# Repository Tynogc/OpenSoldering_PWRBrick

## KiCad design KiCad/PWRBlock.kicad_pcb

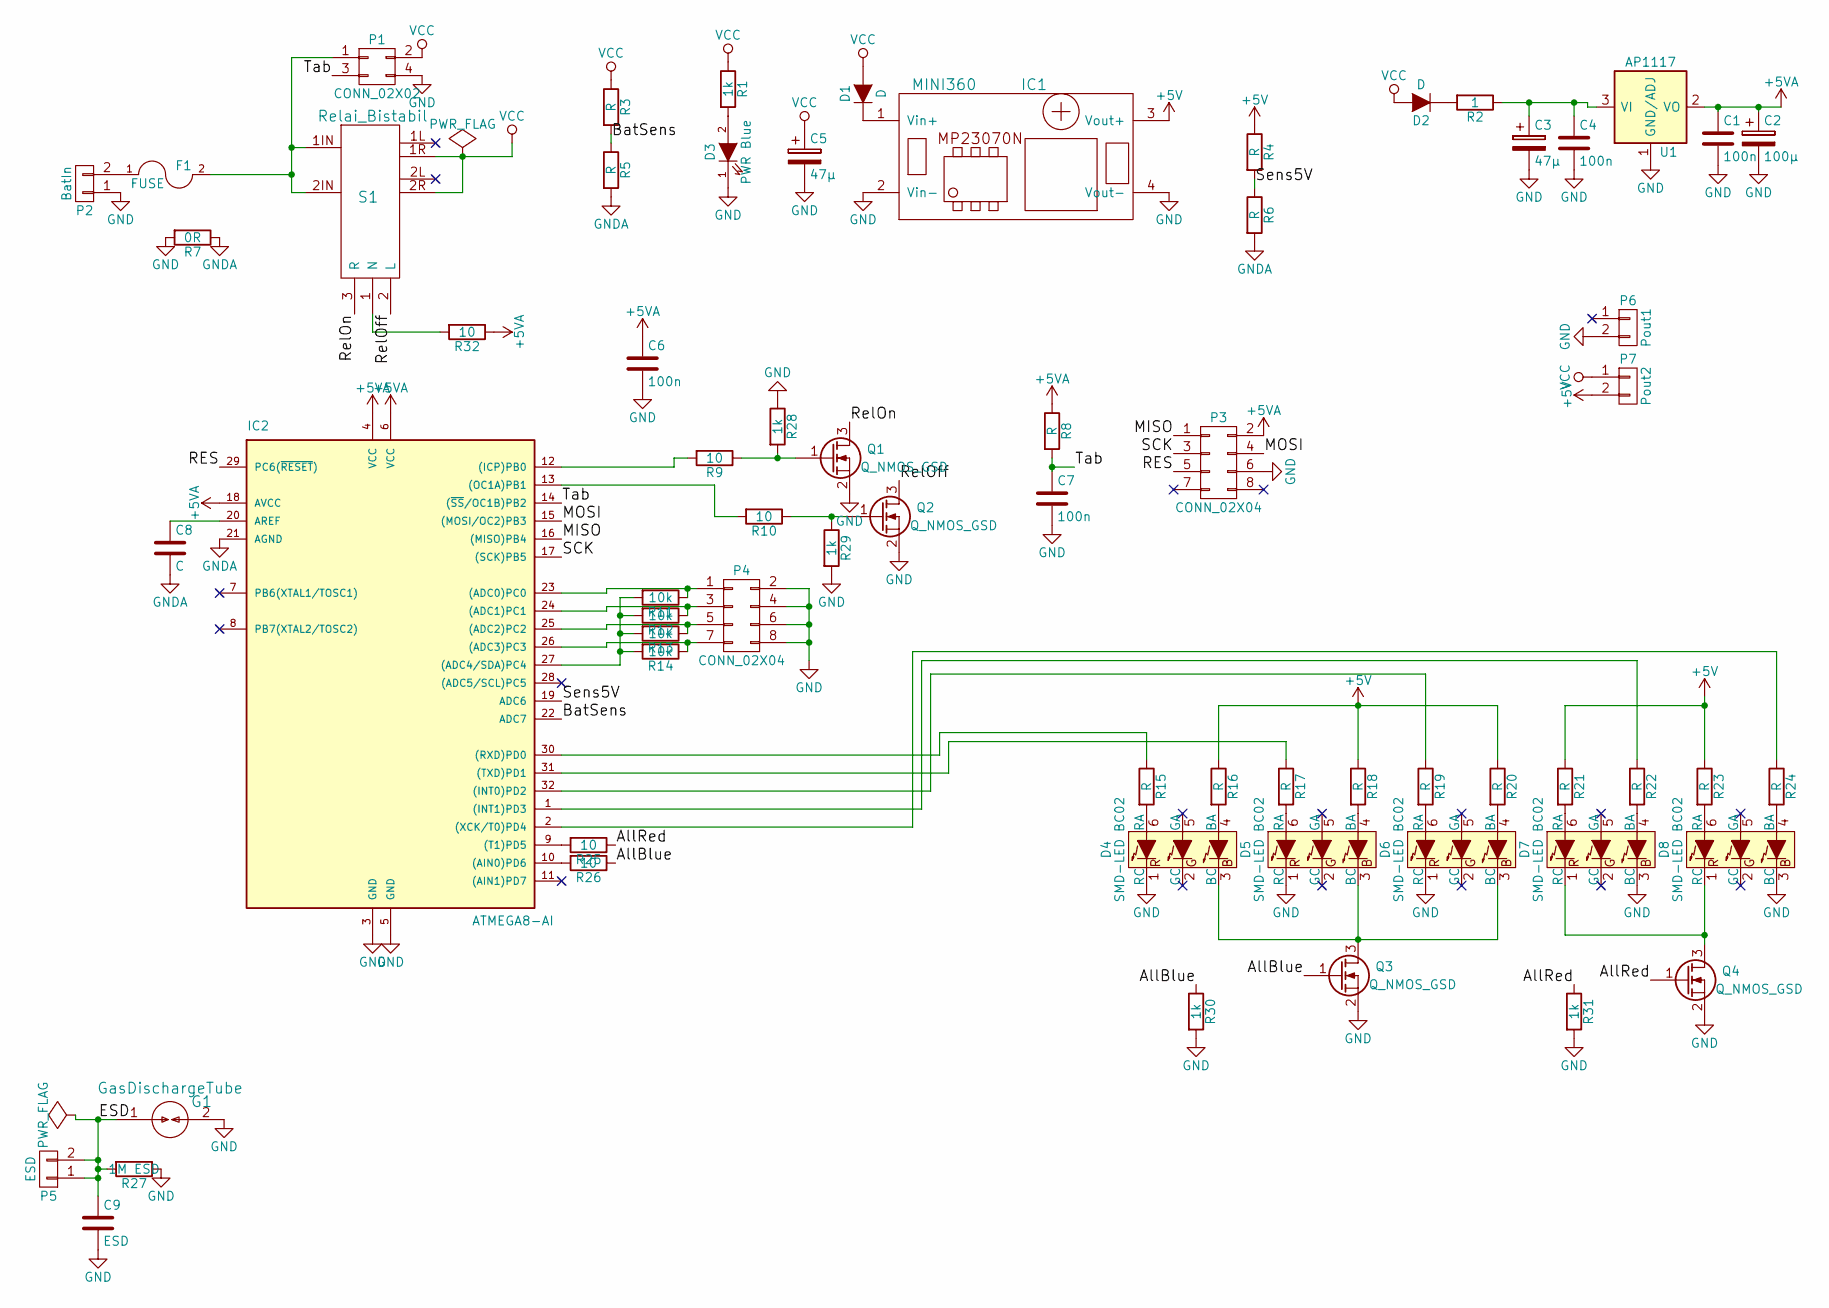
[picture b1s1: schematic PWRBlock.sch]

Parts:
C1, C4, C6, C7: 100n; C_0805
C2: 100µ; C_0805
C3, C5: 47µ; C_Radial_D10_L20_P2.5-5
C8: C; C_0805
C9: ESD; C_Disc_D6_P5
D1, D2: D; SMA-SMB_Universal_Handsoldering
D3: PWR Blue; LED-5MM
D4, D5, D6, D7, D8: SMD-LED BC02; LRTB_G6TG
F1: FUSE; Fuseholder5x20
G1: GasDischargeTube; Socket_Strip_Straight_1x02
IC1: MINI360; Mini360
IC2: ATMEGA8-AI; TQFP-32_7x7mm_Pitch0.8mm
P1: CONN_02X02; Socket_Strip_Straight_2x02
P2: BatIn; Screw_Connector_5,08mm_x2
P3, P4: CONN_02X04; Pin_Header_Straight_2x04
P5: ESD; Screw_Connector_5,08mm_x2
P6: Pout1; Screw_Connector_5,08mm_x2
P7: Pout2; Screw_Connector_5,08mm_x2
Q1, Q2, Q3, Q4: Q_NMOS_GSD; SOT-23_Handsoldering
R1, R28, R29, R30, R31: 1k; R_0805
R2: 1; R_0805
R3, R4, R5, R6, R8, R15, R16, R17, R18, R19, R20, R21, R22, R23, R24: R; R_0805
R7: 0R; R_0805
R9, R10, R25, R26, R32: 10; R_0805
R11, R12, R13, R14: 10k; R_0805
R27: 1M ESD; Resistor_Horizontal_RM15mm
S1: Relai_Bistabil; Relay_DPDT_Schrack-RT2_RM5mm
U1: AP1117; SOT223_GND_VO_VI

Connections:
+5V: IC1.3 (Vout+), P7.2, R4.1, R16.1, R18.1, R20.1, R21.1, R23.1
+5VA: C1.1, C2.1, C6.1, IC2.4 (VCC), IC2.6 (VCC), IC2.18 (AVCC), P3.2, R8.1, R32.1, R32.2, S1.1 (N), U1.2 (VO)
/AllBlue: Q3.1 (G), R26.1, R30.1
/AllRed: Q4.1 (G), R25.1, R31.1
/BatSens: IC2.22 (ADC7), R3.2, R5.1
/ESD: C9.1, G1.1, P5.1, P5.2, R27.2
/MISO: IC2.16 ((MISO)PB4), P3.1
/MOSI: IC2.15 ((MOSI/OC2)PB3), P3.4
/RES: IC2.29 (PC6(~RESET~)), P3.5
/RelOff: Q2.3 (D), S1.2 (L)
/RelOn: Q1.3 (D), S1.3 (R)
/SCK: IC2.17 ((SCK)PB5), P3.3
/Sens5V: IC2.19 (ADC6), R4.2, R6.1
/Tab: C7.1, IC2.14 ((~SS~/OC1B)PB2), P1.3, R8.2
GND: C1.2, C2.2, C3.2, C4.2, C5.2, C6.2, C7.2, C9.2, D3.1 (K), D4.1 (RC), D5.1 (RC), D6.1 (RC), D7.3 (BC), D8.3 (BC), G1.2, IC1.2 (Vin-), IC1.4 (Vout-), IC2.3 (GND), IC2.5 (GND), P1.4, P2.1, P3.6, P4.2, P4.4, P4.6, P4.8, P6.2, Q1.2 (S), Q2.2 (S), Q3.2 (S), Q4.2 (S), R7.2, R27.1, R28.1, R29.2, R30.2, R31.2, U1.1 (GND/ADJ)
GNDA: C8.2, IC2.21 (AGND), R5.2, R6.2, R7.1
unnamed: C3.1, C4.1, R2.1, U1.3 (VI)
unnamed: C8.1, IC2.20 (AREF)
unnamed: D1.1 (K), IC1.1 (Vin+)
unnamed: D2.1 (K), R2.2
unnamed: D3.2 (A), R1.2
unnamed: D4.3 (BC), D5.3 (BC), D6.3 (BC), Q3.3 (D)
unnamed: D4.4 (BA), R16.2
unnamed: D4.6 (RA), R15.2
unnamed: D5.4 (BA), R18.2
unnamed: D5.6 (RA), R17.2
unnamed: D6.4 (BA), R20.2
unnamed: D6.6 (RA), R19.2
unnamed: D7.1 (RC), D8.1 (RC), Q4.3 (D)
unnamed: D7.4 (BA), R22.2
unnamed: D7.6 (RA), R21.2
unnamed: D8.4 (BA), R24.2
unnamed: D8.6 (RA), R23.2
unnamed: F1.1, P2.2
unnamed: F1.2, P1.1, S1.1IN, S1.2IN
unnamed: IC2.1 ((INT1)PD3), R22.1
unnamed: IC2.2 ((XCK/T0)PD4), R24.1
unnamed: IC2.9 ((T1)PD5), R25.2
unnamed: IC2.10 ((AIN0)PD6), R26.2
unnamed: IC2.12 ((ICP)PB0), R9.2
unnamed: IC2.13 ((OC1A)PB1), R10.2
unnamed: IC2.23 ((ADC0)PC0), P4.1, R11.1
unnamed: IC2.24 ((ADC1)PC1), P4.3, R12.1
unnamed: IC2.25 ((ADC2)PC2), P4.5, R13.1
unnamed: IC2.26 ((ADC3)PC3), P4.7, R14.1
unnamed: IC2.27 ((ADC4/SDA)PC4), R11.2, R12.2, R13.2, R14.2
unnamed: IC2.30 ((RXD)PD0), R15.1
unnamed: IC2.31 ((TXD)PD1), R17.1
unnamed: IC2.32 ((INT0)PD2), R19.1
unnamed: Q1.1 (G), R9.1, R28.2
unnamed: Q2.1 (G), R10.1, R29.1
VCC: C5.1, D1.2 (A), D2.2 (A), P1.2, P7.1, R1.1, R3.1, S1.1R, S1.2R

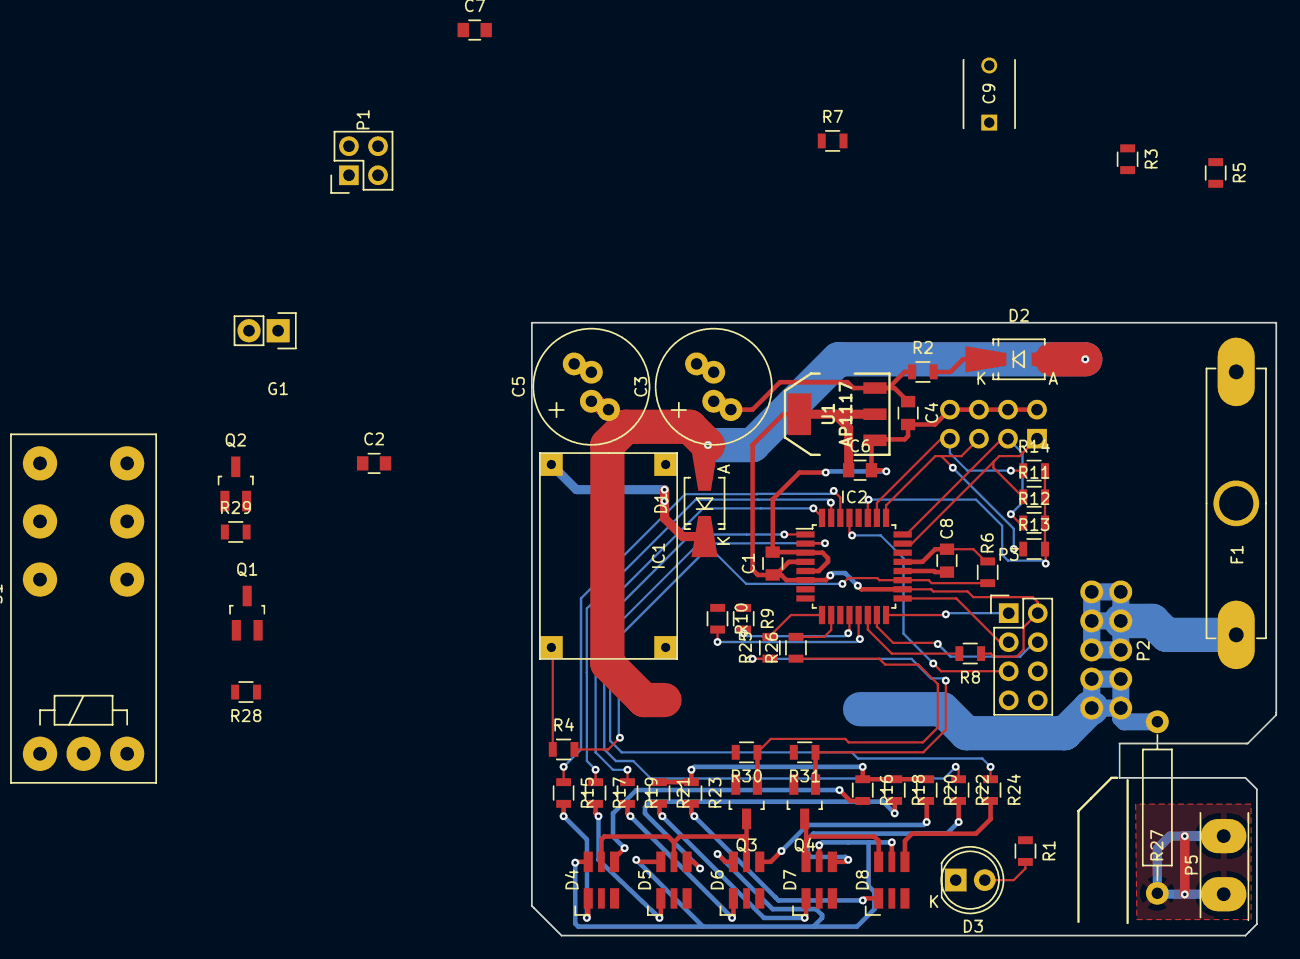
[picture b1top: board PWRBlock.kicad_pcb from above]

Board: 2 copper layers, 65.1 x 53.6 mm, 63 parts (1 on the bottom side), 52 nets.

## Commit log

2015-12-23 Inital commit
2015-12-23 Netztliste erstellt
2015-12-23 PCB angefangen
2016-01-07 LED-footprints
2016-01-07 Platienengröße geändert
